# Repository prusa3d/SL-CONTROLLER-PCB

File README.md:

# PRUSA SL controller board

KiCad PCB layout

* [Interactive bom](http://htmlpreview.github.io/?https://github.com/prusa3d/SL-CONTROLLER-PCB/blob/master/rev.06c/ibom.html)
* [STEP 3D model](rev.06c/SL-controller-06c.step)

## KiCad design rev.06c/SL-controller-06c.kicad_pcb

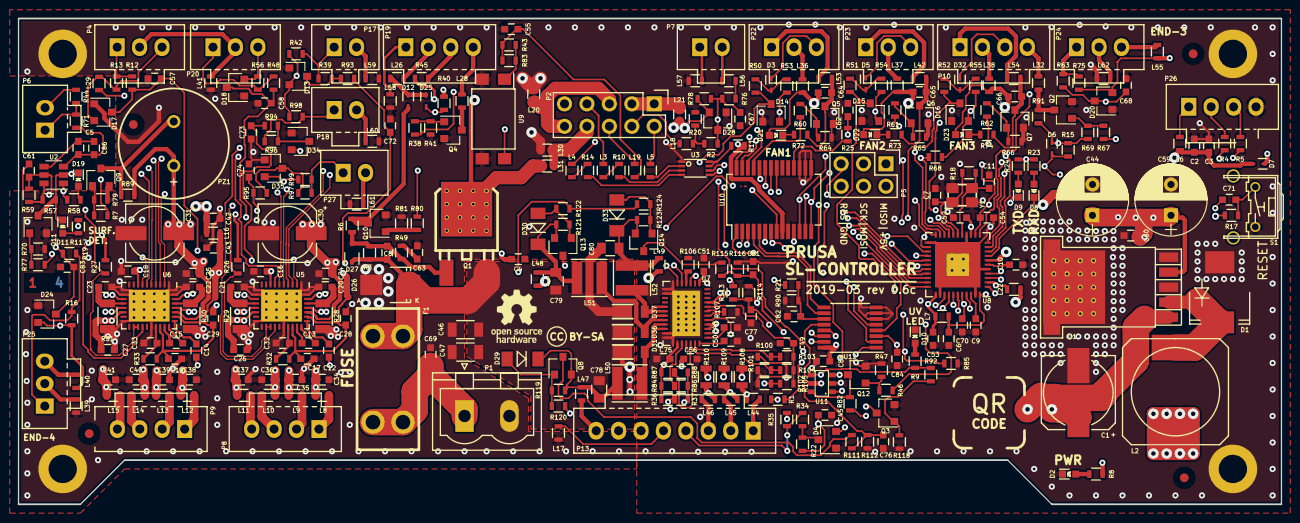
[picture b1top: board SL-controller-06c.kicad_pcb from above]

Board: 4 copper layers, 143.0 x 55.0 mm, 354 parts (0 on the bottom side), 230 nets.

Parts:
C1: 220u; c_elec_8x10.5
C2, C4, C5, C8, C9, C12, C14, C16, C17, C18, C19, C20, C21, C22, C23, C24, C25, C26, C27, C28, C29, C42, C45, C49, C52, C53, C55, C56, C57, C58, C60, C61, C62, C64, C65, C66, C67, C68, C69, C70, C71, C72, C73, C74, C76, C77, C81, C82, C83, C84, C85, C86: 100n; C_0603
C3, C43: 10u; C_0603
C6, C10, C32, C33, C75: 1u/6,3V; C_0603
C7, C11: 22p; C_0603
C13, C15: 22n; C_0603
C30, C31: 100u; c_elec_6.3x7.7
C34, C35, C36, C37, C38, C39, C40, C41, C48, C50, C51: 1n; C_0603
C44, C59: 680u; CP_Radial_D8.0mm_P3.50mm
C46, C47: 2,2u; C_1206
C54: 100n*; C_0603
C63: 1u/35V; C_0603
C78, C79, C80: 330n; C_0805
D1: B540C-13-F; SMC_Standard
D2, D8, D9, D10, D11, D19, D21, D22, D23: GRN; LED_0603-ShortSilk
D3, D5, D6, D7, D12, D25, D32: BAT54KFILM; SOD-523-ShortSilk
D4, D13, D14, D15, D16, D17, D18, D20, D24, D28, D34, D35: BAV99LT1G; SOT-23
D26: SM6T30A; SMB_Standard
D27: MM3Z15VT1G*; SOD-323
D29, D30, D33: ZMM16; MiniMELF_Standard
D31, D36, D37: DFLS140L; PowerDI_123
F1: KEYSTONE 3568; Fuse-Keystone-3557-2
L2: 100uH; SELF-WE-PD-XXL
L3, L4, L5, L6, L7, L8, L9, L10, L11, L12, L13, L14, L15, L16, L17, L18, L19, L20, L21, L22, L26, L28, L29, L30, L32, L36, L37, L38, L39, L40, L41, L42, L44, L45, L46, L47, L48, L49, L53, L54, L55, L56, L57, L58, L59, L60, L61, L62: BLM18KG121TN1D; R_0603
L31: BLM18KG121TN1D*; R_0603
L50, L51, L52: 10uH LQH44PN100MP0L; Inductor_Taiyo-Yuden_MD-4040
P1: TBG-5-PW-2P/GN; PhoenixContact_MSTBVA-G_02x5.08mm_Vertical
P2: DS1024-2.5R0; Pin_Header_Straight_2x05
P3, P11, P12, P21: MP*; MountingHole_3.2mm_M3_ISO14580_Pad
P4, P20, P22, P23, P24, P25: 70543-0002; Pin_1x03-XL
P5: DS1021-2.3SF1-1; Pin_Header_Straight_2x03
P6, P7: MOLEX 70543-0001; Pin_1x02-XL
P8, P9, P10, P19: 70543-0003; Pin_1x04-XL
P13: 70543-0007; Pin_1x08-XL
P17, P18, P27: 70543-0001; Pin_1x02-XL
P26: 70543-0003*; Pin_1x04-XL
PZ1: LD-BZPN-1307; Piezo_12.6_5mm
Q1: FQD11P06TM; DPAK-heatsink
Q2, Q3, Q4, Q5, Q6, Q7, Q9, Q10, Q11, Q12: MMBF170; SOT-23
Q8, Q13, Q14: FDN352AP; SOT-23
Q15: QRcode; QR-code-8x8mm
R1, R7, R12, R19, R38, R46, R48, R60, R61, R62, R63, R67, R77, R80, R92: 100R; R_0603
R2, R37, R59, R86, R88: 0R; R_0603
R3, R11: 200k; R_0603
R4, R5, R10, R14: 22R; R_0603
R6, R8, R9, R23, R24, R49, R58, R76, R83, R117: 1k; R_0603
R13, R15, R16, R17, R21, R25, R26, R27, R56, R69, R72, R73, R74, R75, R78, R82, R91, R106: 10k; R_0603
R18: 1M; R_0603
R20: 21k; R_0603
R22, R34, R39, R50, R51, R52, R53, R54, R55, R90, R93, R94, R95, R96, R97: 1k8; R_0603
R28, R29, R30, R31: R22; R_1206
R32, R33: 10R; R_0603
R35, R112, R114, R116, R120, R122, R124: 33k; R_0603
R36, R84, R87: 10k*; R_0603
R40, R41, R47, R64, R65, R66, R70, R79, R81, R85, R89, R118, R119, R121, R123: 100k; R_0603
R42, R98, R99: 82k; R_0603
R43: 1k*; R_0603
R44: 100k*; R_0603
R45: 330R; R_0603
R57: 0R*; R_0603
R68: 2k2*; R_0603
R71: 3k6; R_0603
R100, R101, R102, R111, R113, R115: 47k; R_0603
R103, R104, R105: 15k; R_0603
R107: 68k; R_0603
R108, R109, R110: 0,1R; R_0805
S1: TACTA-64N-F; TACT-90
U1: LM2576; TO-263-5-heatsink
U2: AT42QT1011-TSHR; SOT-23-6
U3: LSF0102
U5, U6: TMC2130-LA; QFN-36-1EP_5x6mm_Pitch0.5mm-GNDpad-0.3mm
U7: LT3476; QFN-38-1EP_5x7mm_Pitch0.5mm
U8: ATmega32U4; QFN-44-1EP_7x7mm_Pitch0.5mm
U9: EL817S1; Optocoupler_SMD_LTV-817S
U10: MCP23S17-E/SS; SSOP-28_5.3x10.2mm_Pitch0.65mm
U11: 74LVC1G11GV.125; SOT457
U12: 74HCT4052PW.118; TSSOP-16_4.4x5mm_Pitch0.65mm
Y1: LFXTAL035264REEL; Crystal-3.2x2.5mm

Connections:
3V3_ref: L5.2, U3.2
24VDC: C8.1, C46.1, C47.1, C78.2, C79.2, C80.2, D26.1, D27.1, D31.1, D36.1, D37.1, F1.1, Q1.3, R3.1, R108.2, R109.2, R110.2, U7.3, U7.4, U7.9
+5V: C42.1, C44.1, C56.1, C59.1, C60.1, C61.2, C62.1, C75.1, C85.2, D4.2, D6.1, D7.1, D13.2, D14.2, D15.2, D16.2, D20.2, D24.2, D28.2, D34.2, D35.2, L2.2, L16.1, L21.2, L22.1, L29.1, L40.1, L55.1, P5.2, R8.1, R11.1, R15.2, R16.2, R17.2, R23.1, R24.1, R25.1, R26.1, R27.1, R35.1, R36.1, R40.2, R42.1, R53.2, R54.2, R55.2, R59.2, R68.2, R69.1, R75.1, R78.2, R82.1, R84.1, R87.1, R91.1, R98.1, R99.1, R117.2, U1.4, U2.5, U7.33, U10.9, U11.5, U12.16
+5V-MOT: C16.1, C17.1, C18.1, C19.1, C28.1, C29.1, C43.1, L16.2, R32.1, R33.1, U5.8, U5.26, U5.30, U6.8, U6.26, U6.30
+24V: C1.1, C4.2, C12.1, C14.1, C24.1, C25.1, C26.1, C27.1, C30.1, C31.1, C64.2, C65.2, C66.2, D21.2, D22.2, D23.2, L31.2, L36.2, L37.2, L38.2, PZ1.1, Q1.2, R21.1, R45.1, R89.1, U1.1, U5.16, U5.31, U6.16, U6.31
/4-chanel-LED-PWR/MP1: C78.1, D29.1, L47.2, L50.1, Q8.2, R119.1
/4-chanel-LED-PWR/MP2: C79.1, D30.1, L48.2, L51.1, Q13.2, R121.1
/4-chanel-LED-PWR/MP3: C80.1, D33.1, L49.2, L52.1, Q14.2, R123.1
/D+: R5.2, U8.4
/D-: R4.1, U8.3
/ENABLE: R9.2, R92.2, U7.18, U11.4
/LED1+: L44.2, P13.1
/LED1-_1: L47.1, P13.8
/LED2+: L45.2, P13.2
/LED2-_1: L48.1, P13.7
/LED3+: L46.2, P13.3
/LED3-: L49.1, P13.6
/PWM2: R1.2, R37.1, R86.1, R88.1
/RESET: C54.1, C71.1, D6.2, P5.5, R15.1, U8.13, U9.4
/VBUS: C2.2, C3.2, D7.2, L6.2, U8.7
A64-IN: L18.2, R2.1, R20.2
A64-OUT: C55.1, L19.2, R43.1, R83.1
AnalogSwA: U10.4, U12.10
AnalogSwB: U10.5, U12.9
BUTT-DETECT: D25.2, R40.1, U10.8
BUZZ: R7.1, U8.31
CS-MCP: U8.28, U10.11
CSN-1: U5.2, U8.19
CSN-2: U6.2, U8.25
D0(RXD): R68.1, U3.5, U8.20
D1(TXD): U3.6, U8.21
DC-voltage: C82.1, R21.2, R90.1, U12.11
DIR-1: U5.7, U10.21
DIR-2: U6.7, U10.23
Diag-1: R26.2, U5.20, U5.21, U8.26
Diag-2: R27.2, U6.20, U6.21, U8.27
EN-1: U5.22, U10.22
EN-2: U6.22, U10.24
END1: C57.1, D17.3, R12.2, R46.1, U10.7
END2: C58.1, D18.3, R48.2, U10.6
END3: C68.2, D20.3, R63.2, U10.28
END4: C83.1, D24.3, R19.1, U10.2
FAN1: R60.1, U10.25
FAN1-TACH: D14.3, R50.1, U8.39
FAN2: R61.1, U10.26
FAN2-TACH: D15.3, R51.1, U8.38
FAN3: R62.1, U10.27
FAN3-PWM: R67.1, U8.36
FAN3-TACH: D16.3, R52.1, U8.37
GND: C1.2, C2.1, C3.1, C4.1, C6.1, C7.2, C9.1, C10.1, C11.2, C16.2, C17.2, C18.2, C19.2, C20.2, C21.2, C22.2, C23.2, C24.2, C25.2, C26.2, C27.2, C28.2, C29.2, C30.2, C31.2, C32.1, C33.1, C34.1, C35.1, C36.1, C37.1, C38.1, C39.1, C40.1, C41.1, C42.2, C43.2, C44.2, C45.2, C46.2, C47.2, C48.1, C49.2, C50.1, C51.1, C52.2, C53.2, C54.2, C55.2, C56.2, C57.2, C58.2, C59.2, C60.2, C61.1, C62.2, C63.2, C67.2, C68.1, C69.2, C70.1, C72.2, C73.2, C74.2, C75.2, C76.1, C77.1, C81.1, C82.2, C83.2, C84.1, C85.1, D1.2, D2.1, D4.1, D10.1, D13.1, D14.1, D15.1, D16.1, D17.1, D18.1, D20.1, D24.1, D26.2, D28.1, D34.1, D35.1, L17.2, L20.2, L30.1, L39.1, L41.2, L57.2, L58.2, L59.2, L60.2, L61.2, L62.1, P1.2, P3.1, P5.6, P11.1, P12.1, P21.1, P26.4, Q2.2, Q3.2, Q4.2, Q5.2, Q6.2, Q7.2, Q9.2, Q10.2, Q11.2, Q12.2, R20.1, R28.1, R29.1, R30.1, R31.1, R41.2, R47.1, R64.2, R65.2, R66.2, R70.2, R79.2, R81.2, R85.2, R90.2, R100.2, R101.2, R102.2, R106.1, R107.1, R112.2, R114.2, R116.2, R118.2, S1.2, U1.3, U1.5, U3.1, U5.1, U5.11, U5.12, U5.18, U5.24, U5.35, U5.36, U5.37, U6.1, U6.11, U6.12, U6.18, U6.24, U6.35, U6.36, U6.37, U7.19, U7.20, U7.21, U7.30, U7.31, U7.32, U7.39, U8.5, U8.15, U8.23, U8.35, U8.43, U9.2, U9.3, U10.10, U10.15, U10.16, U10.17, U11.2, U12.6, U12.7, U12.8, Y1.2, Y1.4
MISO: P5.1, U5.5, U6.5, U8.11, U10.14
MOSI: P5.4, U5.4, U6.4, U8.10, U10.13
unnamed: C5.1, C86.1, R71.2, U2.3
unnamed: C5.2, C86.2, U2.4
unnamed: C6.2, L7.1, U8.24, U8.44
unnamed: C7.1, R18.2, U8.17, Y1.1
unnamed: C8.2, D27.2, Q1.1, R3.2, R6.1, R49.1
unnamed: C9.2, U8.42
unnamed: C10.2, U8.6
unnamed: C11.1, R18.1, U8.16, Y1.3
unnamed: C12.2, U5.29
unnamed: C13.1, U5.27
unnamed: C13.2, U5.28
unnamed: C14.2, U6.29
unnamed: C15.1, U6.27
unnamed: C15.2, U6.28
unnamed: C20.1, R28.2, U5.33
unnamed: C21.1, R29.2, U5.14
unnamed: C22.1, R30.2, U6.33
unnamed: C23.1, R31.2, U6.14
unnamed: C32.2, R32.2, U5.25
unnamed: C33.2, R33.2, U6.25
unnamed: C34.2, L8.1, U5.32
unnamed: C35.2, L9.1, U5.34
unnamed: C36.2, L10.1, U5.15
unnamed: C37.2, L11.1, U5.13
unnamed: C38.2, L12.1, U6.32
unnamed: C39.2, L13.1, U6.34
unnamed: C40.2, L14.1, U6.15
unnamed: C41.2, L15.1, U6.13
unnamed: C48.2, U7.1
unnamed: C49.1, R103.1, R104.1, R105.1, U7.7
unnamed: C50.2, U7.38
unnamed: C51.2, U7.13
unnamed: C52.1, C53.1, L7.2, L22.2, U8.2, U8.14, U8.34
unnamed: C63.1, R49.2
unnamed: C64.1, L53.2, Q5.3, R72.1
unnamed: C65.1, L42.2, Q6.3, R73.1
unnamed: C66.1, L54.2, Q7.3, R74.1
unnamed: C69.1, F1.2, P1.1
unnamed: C71.2, R17.1, S1.1
unnamed: D1.1, L2.1, U1.2
unnamed: D2.2, R8.2
unnamed: D3.1, P22.3
unnamed: D3.2, R50.2, R53.1
unnamed: D4.3, R22.2, R34.1
unnamed: D5.1, P23.3
unnamed: D5.2, R51.2, R54.1
unnamed: D8.1, U8.8
unnamed: D8.2, R23.2
unnamed: D9.1, U8.22
unnamed: D9.2, R24.2
unnamed: D10.2, R9.1
unnamed: D11.1, D19.1, P6.2, Q11.3, R44.2, R57.1, U2.2
unnamed: D11.2, R117.1
unnamed: D12.1, D25.1, L26.2
unnamed: D13.3, R39.1, R93.2
unnamed: D17.2, D18.2, L29.2, P4.3, P20.3, R13.1, R56.1
unnamed: D19.2, R58.1
unnamed: D21.1, R72.2
unnamed: D22.1, R73.2
unnamed: D23.1, R74.2
unnamed: D29.2, Q8.1, R119.2, R120.1
unnamed: D30.2, Q13.1, R121.2, R122.1
unnamed: D31.2, L50.2, U7.28, U7.29
unnamed: D32.1, P10.3
unnamed: D32.2, R52.2, R55.1
unnamed: D33.2, Q14.1, R123.2, R124.1
unnamed: D34.3, R94.2, R96.1
unnamed: D35.3, R95.2, R97.1
unnamed: D36.2, L51.2, U7.26, U7.27
unnamed: D37.2, L52.2, U7.24, U7.25
unnamed: L3.1, P2.7
unnamed: L3.2, R10.2
unnamed: L4.1, P2.9
unnamed: L4.2, R14.2
unnamed: L5.1, P2.2
unnamed: L6.1, P26.1
unnamed: L8.2, P8.1
unnamed: L9.2, P8.2
unnamed: L10.2, P8.3
unnamed: L11.2, P8.4
unnamed: L12.2, P9.1
unnamed: L13.2, P9.2
unnamed: L14.2, P9.3
unnamed: L15.2, P9.4
unnamed: L17.1, P13.5
unnamed: L18.1, P2.4
unnamed: L19.1, P2.6
unnamed: L20.1, P2.5, P2.10
unnamed: L21.1, P2.1, P2.3
unnamed: L26.1, P19.2
unnamed: L28.1, P19.4
unnamed: L28.2, Q4.3
unnamed: L30.2, L31.1, P2.8
unnamed: L32.1, Q2.3, R91.2
unnamed: L32.2, P10.4
unnamed: L36.1, P22.2
unnamed: L37.1, P23.2
unnamed: L38.1, P10.2
unnamed: L39.2, P25.2
unnamed: L40.2, P25.3
unnamed: L41.1, P4.2, P20.2
unnamed: L42.1, P23.1
unnamed: L44.1, R108.1, U7.2
unnamed: L45.1, R109.1, U7.5
unnamed: L46.1, R110.1, U7.8
unnamed: L53.1, P22.1
unnamed: L54.1, P10.1
unnamed: L55.2, P24.3
unnamed: L56.1, R76.2
unnamed: L56.2, P7.2
unnamed: L57.1, P7.1
unnamed: L58.1, P19.1
unnamed: L59.1, P17.2
unnamed: L60.1, P18.2
unnamed: L61.1, P27.2
unnamed: L62.2, P24.2
unnamed: P4.1, R12.1, R13.2
unnamed: P6.1, R44.1, R71.1
unnamed: P13.4, R34.2, R35.2
unnamed: P17.1, R39.2, R42.2
unnamed: P18.1, R96.2, R98.2
unnamed: P19.3, R45.2
unnamed: P20.1, R48.1, R56.2
unnamed: P24.1, R63.1, R75.2
unnamed: P25.1, R16.1, R19.2
unnamed: P26.2, R4.2
unnamed: P26.3, R5.1
unnamed: P27.1, R97.2, R99.2
unnamed: PZ1.2, Q9.3, R89.2
unnamed: Q2.1, R67.2, R69.2
unnamed: Q3.1, R92.1, R118.1
unnamed: Q3.3, R120.2, R122.2, R124.2
unnamed: Q4.1, R38.2, R41.1
unnamed: Q5.1, R60.2, R64.1
unnamed: Q6.1, R61.2, R65.1
unnamed: Q7.1, R62.2, R66.1
unnamed: Q8.3, R111.2
unnamed: Q9.1, R7.2, R79.1
unnamed: Q10.1, R80.2, R81.1
unnamed: Q11.1, R70.1, R77.1
unnamed: Q12.1, R46.2, R47.2
unnamed: Q12.3, R82.2, U11.6
unnamed: Q13.3, R113.2
unnamed: Q14.3, R115.2
unnamed: R10.1, U3.3
unnamed: R11.2, U3.7, U3.8
unnamed: R14.1, U3.4
unnamed: R25.2, U10.18
unnamed: R36.2, R37.2, U7.17
unnamed: R43.2, R83.2, U9.1
unnamed: R57.2, R59.1, U2.6
unnamed: R84.2, R86.2, U7.34
unnamed: R87.2, R88.2, U7.35
unnamed: R100.1, R103.2, U7.37
unnamed: R101.1, R104.2, U7.36
unnamed: R102.1, R105.2, U7.15
unnamed: R106.2, U7.16
unnamed: R107.2, U7.6
PANIC: C67.1, D28.3, R2.2, R76.1, R78.1, U8.1, U11.1
PWR-BON: D12.2, Q10.3, R6.2
PWR-ON: R80.1, U8.32
SCK: P5.3, U5.3, U6.3, U8.9, U10.12
START-LED: R38.1, U8.12
Step-1: U5.6, U8.29
Step-2: U6.6, U8.30
Surface-detector: R58.2, U2.1, U8.33
TEMP-1: C72.1, R93.1, U12.5
TEMP-2: C73.1, R94.1, U12.2
TEMP-3: C74.1, R95.1, U12.4
TEMP-LED: C45.1, R22.1, U12.1
TEMP-MULTIPLEX: C84.2, U8.41, U12.3
UV-LED: R85.1, U10.1, U11.3
UV-LED-1: C76.2, R111.1, R112.1, U12.12
UV-LED-2: C77.2, R113.1, R114.1, U12.14
UV-LED-3: C81.2, R115.1, R116.1, U12.15
UV-LED-MULTIPLEX: C70.2, U8.40, U12.13
UV-LED-PWM: R1.1, U8.18
detect-ON: R77.2, U10.3

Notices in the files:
rev.06c/SL-controller-06c.kicad_pcb:
CC BY-SA
